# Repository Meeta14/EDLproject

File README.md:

# EDLproject

Contains the code for measuring the State-of-Charge (SoC) of Lead-acid battery and also the PCB design of an analog circuit designed for LED intensity control of Solar-powered street lights.

Below are the schematic and board diagrams of the above-mentioned PCB.

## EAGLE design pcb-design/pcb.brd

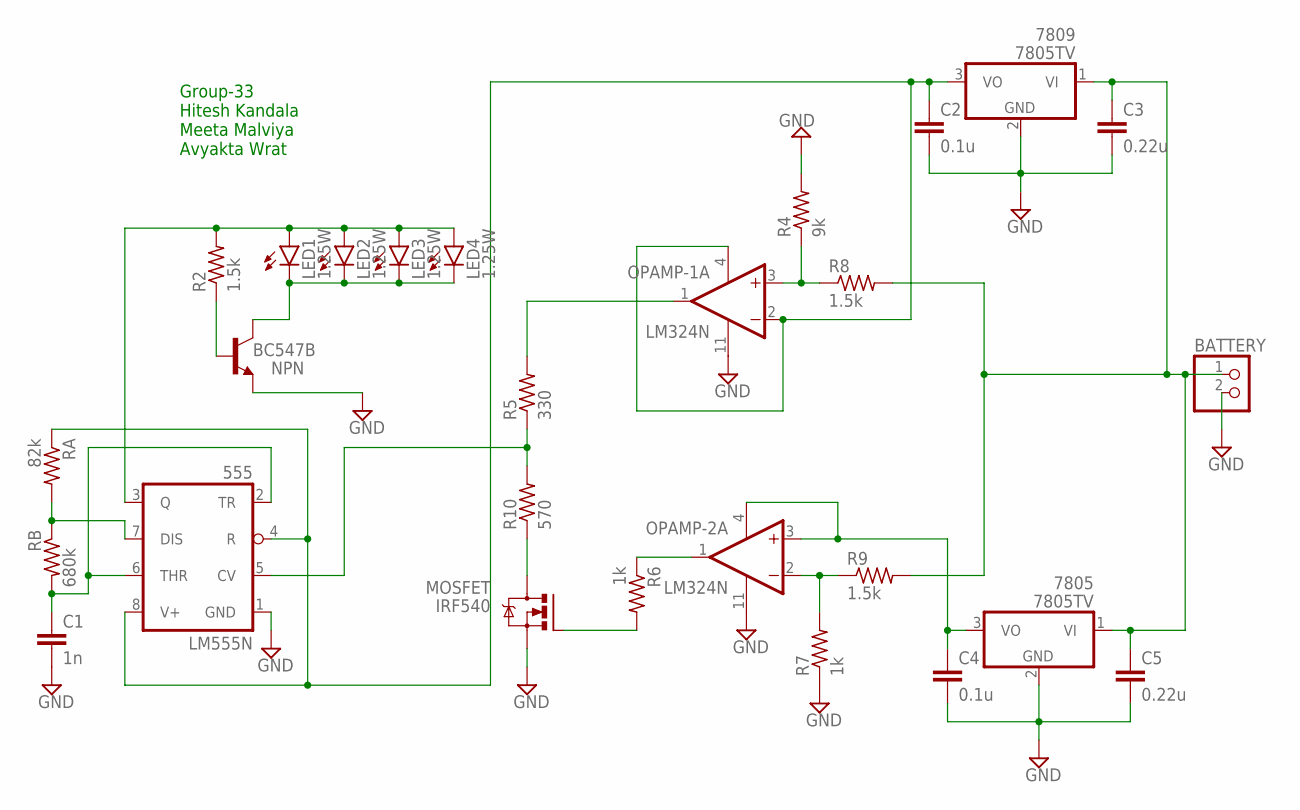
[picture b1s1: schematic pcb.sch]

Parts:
555: LM555N; DIL08
7805, 7809: 7805TV; TO220V
BATTERY: PINHD-1X2; 1X02
C1: 1n; C050-025X075
C2, C4: 0.1u; C050-025X075
C3, C5: 0.22u; C050-025X075
LED1, LED2, LED3, LED4: 1.25W; LED5MM
MOSFET: IRF540; TO220BV
NPN: BC547B; TO92
OPAMP-1, OPAMP-2: LM324N; DIL14
R2, R8, R9: 1.5k; 0207/10
R4: 9k; 0207/10
R5: 330; 0207/10
R6, R7: 1k; 0207/10
R10: 570; 0207/10
RA: 82k; 0207/10
RB: 680k; 0207/10

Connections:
GND: 555.1 (GND), 7805.2 (GND), 7809.2 (GND), BATTERY.2, C1.2, C2.2, C3.2, C4.2, C5.2, MOSFET.S, NPN.1 (E), OPAMP-1.11 (V-), OPAMP-2.11 (V-), R4.2, R7.1
unnamed: 555.4 (R), 555.8 (V+), 7809.3 (VO), C2.1, OPAMP-1.2 (-IN), OPAMP-1.4 (V+), RA.1
unnamed: 555.2 (TR), 555.6 (THR), C1.1, RB.2
unnamed: 555.3 (Q), LED1.A, LED2.A, LED3.A, LED4.A, R2.2
unnamed: 555.7 (DIS), RA.2, RB.1
unnamed: 7805.1 (VI), 7809.1 (VI), BATTERY.1, C3.1, C5.1, R8.2, R9.2
unnamed: NPN.2 (B), R2.1
unnamed: OPAMP-1.3 (+IN), R4.1, R8.1
unnamed: OPAMP-2.2 (-IN), R7.2, R9.1
unnamed: 7805.3 (VO), C4.1, OPAMP-2.3 (+IN), OPAMP-2.4 (V+)
unnamed: OPAMP-2.1 (OUT), R6.1
unnamed: 555.5 (CV), R5.1, R10.2
unnamed: OPAMP-1.1 (OUT), R5.2
unnamed: MOSFET.D, R10.1
unnamed: MOSFET.G, R6.2
unnamed: LED1.K (C), LED2.K (C), LED3.K (C), LED4.K (C), NPN.3 (C)

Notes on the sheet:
Group-33 Hitesh Kandala Meeta Malviya Avyakta Wrat

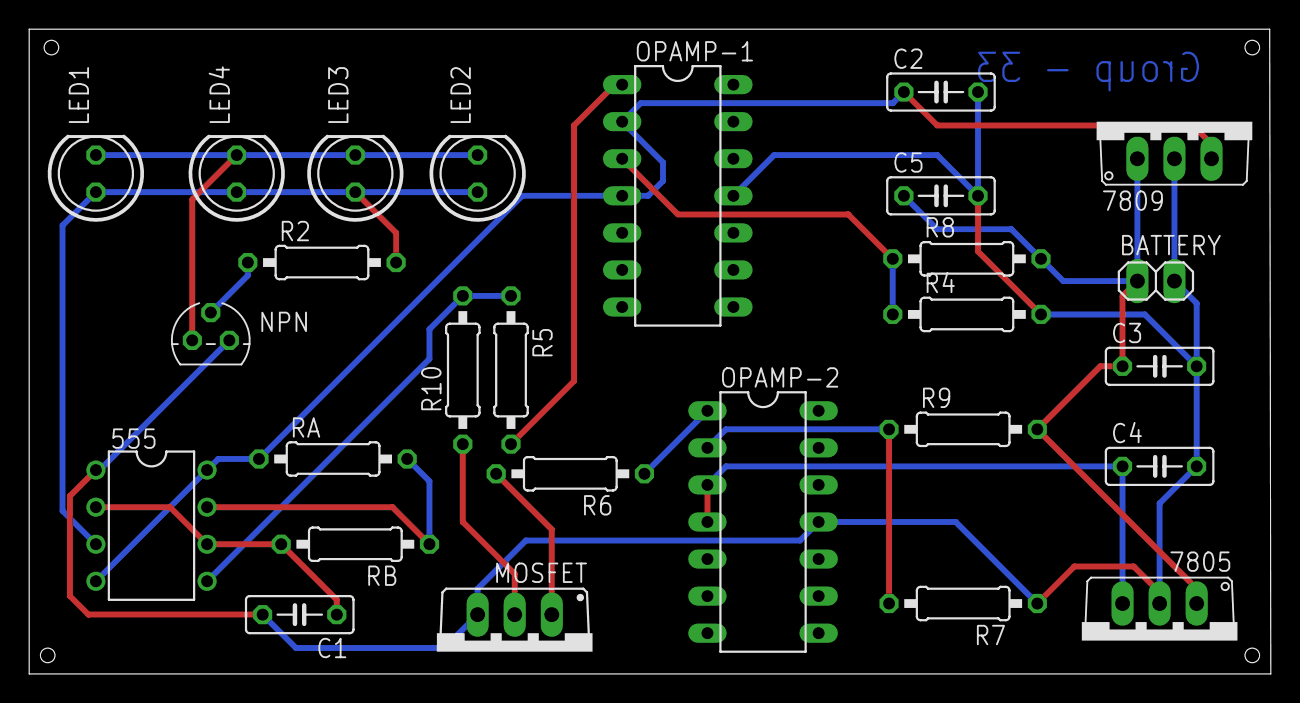
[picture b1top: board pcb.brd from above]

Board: 2 copper layers, 85.1 x 44.2 mm, 27 parts (0 on the bottom side), 16 nets.

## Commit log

2021-04-15 pcb-design
2021-04-15 added diagrams in readme
2021-04-17 report added
2021-04-20 report updated
